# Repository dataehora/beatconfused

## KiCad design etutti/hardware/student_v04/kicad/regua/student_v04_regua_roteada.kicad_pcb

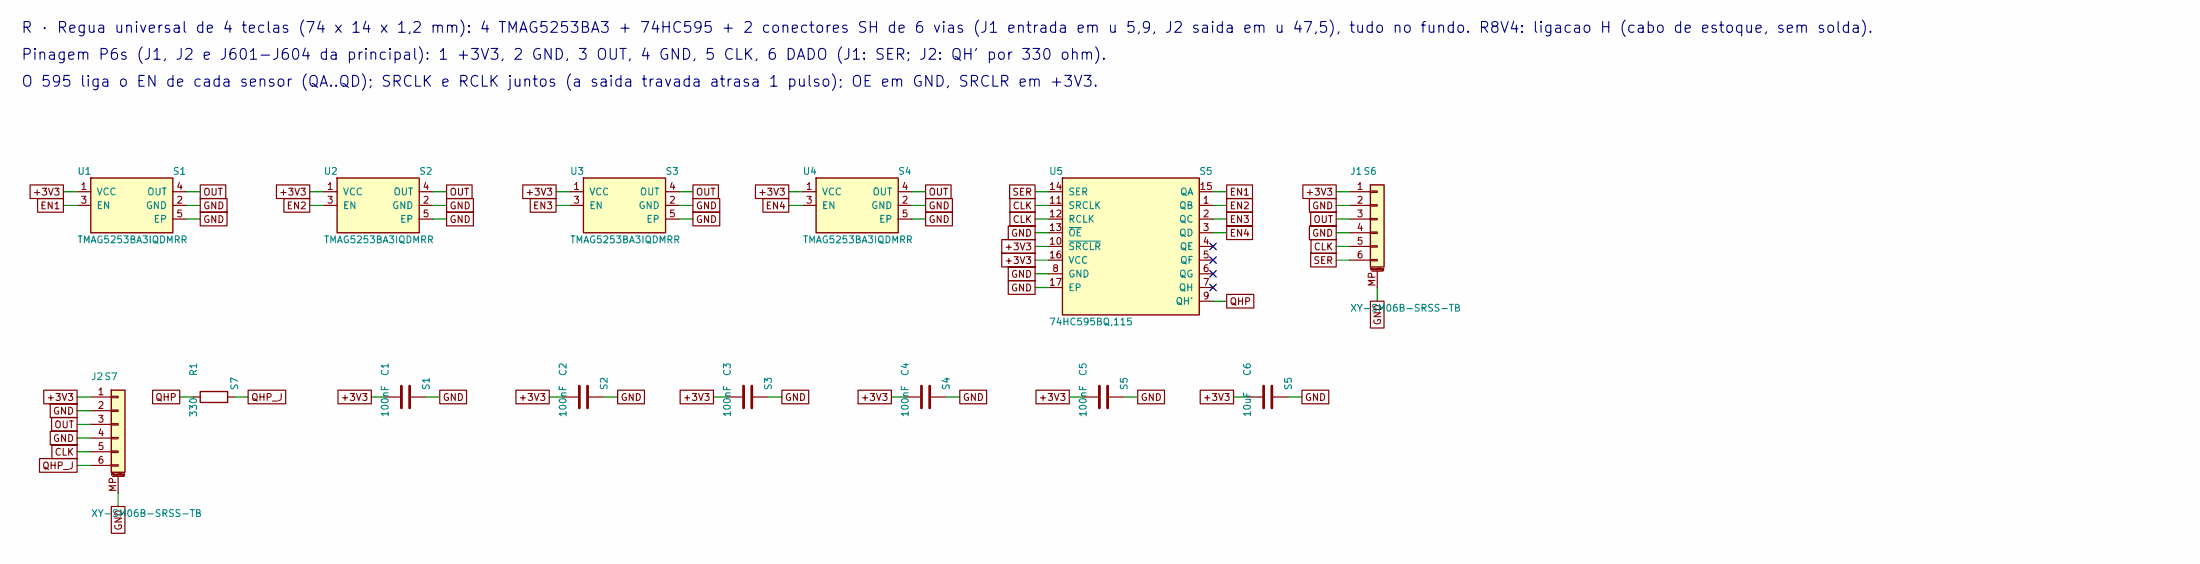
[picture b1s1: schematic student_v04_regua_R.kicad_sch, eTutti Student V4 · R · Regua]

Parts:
C1, C2, C3, C4, C5: 100nF; C_0402_1005Metric; LCSC C1525
C6: 10uF; C_0805_2012Metric; LCSC C15850
J1, J2: XY-SM06B-SRSS-TB; JST_SH_SM06B-SRSS-TB_1x06-1MP_P1.00mm_Horizontal; LCSC C56123098
R1: 330; R_0402_1005Metric; LCSC C25104
U1, U2, U3, U4: TMAG5253BA3IQDMRR; Texas_X2SON-4-1EP_1.1x1.4mm_P0.5mm_EP0.8x0.6mm; LCSC C22401868
U5: 74HC595BQ,115; DHVQFN-16-1EP_2.5x3.5mm_P0.5mm_EP1x2mm; LCSC C730243

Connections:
+3V3: C1.1, C2.1, C3.1, C4.1, C5.1, C6.1, J1.1, J2.1, U1.1 (VCC), U2.1 (VCC), U3.1 (VCC), U4.1 (VCC), U5.10 (~SRCLR), U5.16 (VCC)
CLK: J1.5, J2.5, U5.11 (SRCLK), U5.12 (RCLK)
EN1: U1.3 (EN), U5.15 (QA)
EN2: U2.3 (EN), U5.1 (QB)
EN3: U3.3 (EN), U5.2 (QC)
EN4: U4.3 (EN), U5.3 (QD)
GND: C1.2, C2.2, C3.2, C4.2, C5.2, C6.2, J1.2, J1.4, J1.MP (MountPin), J2.2, J2.4, J2.MP (MountPin), U1.2 (GND), U1.5 (EP), U2.2 (GND), U2.5 (EP), U3.2 (GND), U3.5 (EP), U4.2 (GND), U4.5 (EP), U5.8 (GND), U5.13 (~OE), U5.17 (EP)
OUT: J1.3, J2.3, U1.4 (OUT), U2.4 (OUT), U3.4 (OUT), U4.4 (OUT)
QHP: R1.1, U5.9 (QH')
QHP_J: J2.6, R1.2
SER: J1.6, U5.14 (SER)

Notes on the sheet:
R · Regua universal de 4 teclas (74 x 14 x 1,2 mm): 4 TMAG5253BA3 + 74HC595 + 2 conectores SH de 6 vias (J1 entrada em u 5,9, J2 saida em u 47,5), tudo no fundo. R8V4: ligacao H (cabo de estoque, sem solda).
Pinagem P6s (J1, J2 e J601-J604 da principal): 1 +3V3, 2 GND, 3 OUT, 4 GND, 5 CLK, 6 DADO (J1: SER; J2: QH' por 330 ohm).
O 595 liga o EN de cada sensor (QA..QD); SRCLK e RCLK juntos (a saida travada atrasa 1 pulso); OE em GND, SRCLR em +3V3.

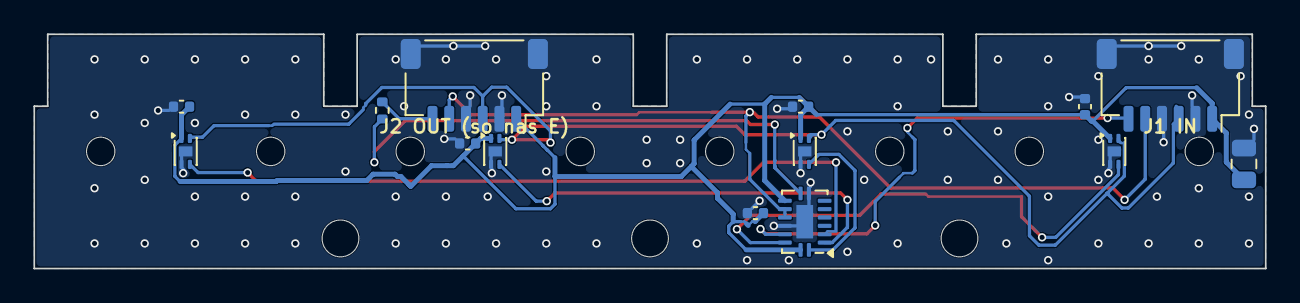
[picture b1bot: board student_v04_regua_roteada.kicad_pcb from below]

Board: 2 copper layers, 73.6 x 14.0 mm, 25 parts (14 on the bottom side), 11 nets.

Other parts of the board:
H1, H2, H3: MountingHole_2.2mm_M2
PEG1a, PEG1b, PEG2a, PEG2b, PEG3a, PEG3b, PEG4a, PEG4b: MountingHole_2.2mm_M2

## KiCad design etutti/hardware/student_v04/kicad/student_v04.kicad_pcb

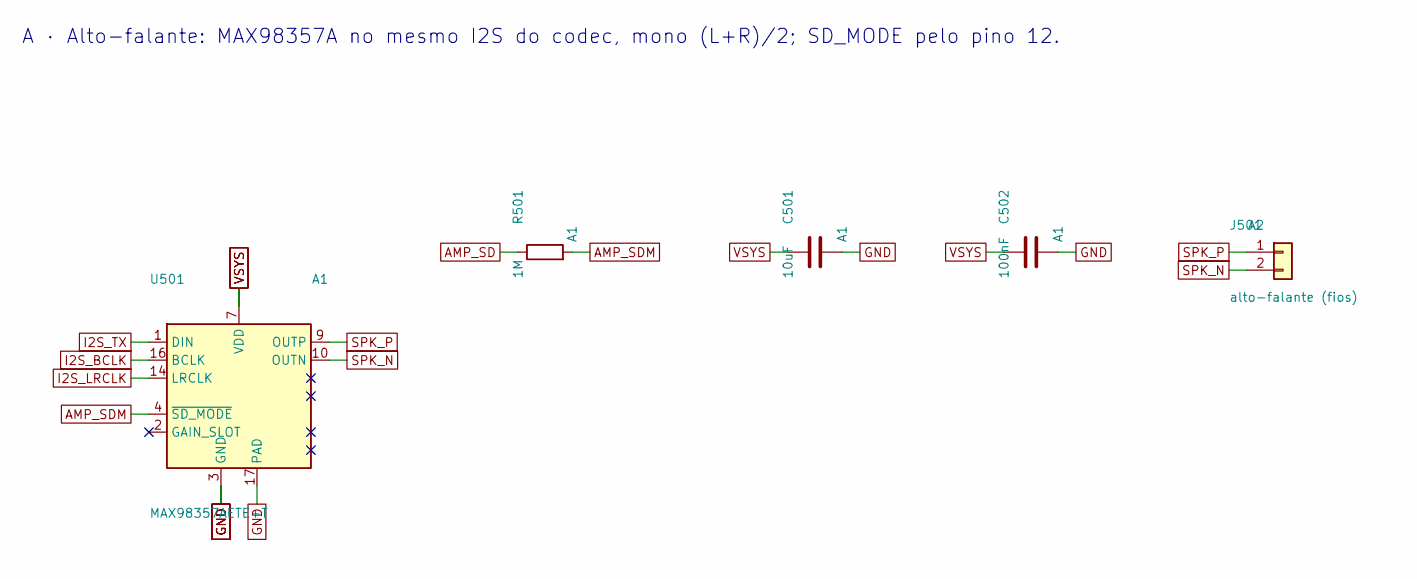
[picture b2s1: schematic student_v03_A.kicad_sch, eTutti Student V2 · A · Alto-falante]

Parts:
C501: 10uF; C_0805_2012Metric; LCSC C15850
C502: 100nF; C_0402_1005Metric; LCSC C1525
J501: alto-falante (fios); SolderWire-0.127sqmm_1x02_P3.7mm_D0.48mm_OD1mm
R501: 1M; R_0402_1005Metric; LCSC C26083
U501: MAX98357AETE+T; TQFN-16-1EP_3x3mm_P0.5mm_EP1.23x1.23mm; LCSC C910544

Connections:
AMP_SD: R501.1; also elsewhere on the board
AMP_SDM: R501.2, U501.4 (~SD_MODE)
GND: C501.2, C502.2, U501.3 (GND), U501.11 (GND), U501.15 (GND), U501.17 (PAD); also elsewhere on the board
I2S_BCLK: U501.16 (BCLK); also elsewhere on the board
I2S_LRCLK: U501.14 (LRCLK); also elsewhere on the board
I2S_TX: U501.1 (DIN); also elsewhere on the board
SPK_N: J501.2, U501.10 (OUTN)
SPK_P: J501.1, U501.9 (OUTP)
VSYS: C501.1, C502.1, U501.7 (VDD), U501.8 (VDD); also elsewhere on the board

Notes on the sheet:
A · Alto-falante: MAX98357A no mesmo I2S do codec, mono (L+R)/2; SD_MODE pelo pino 12.

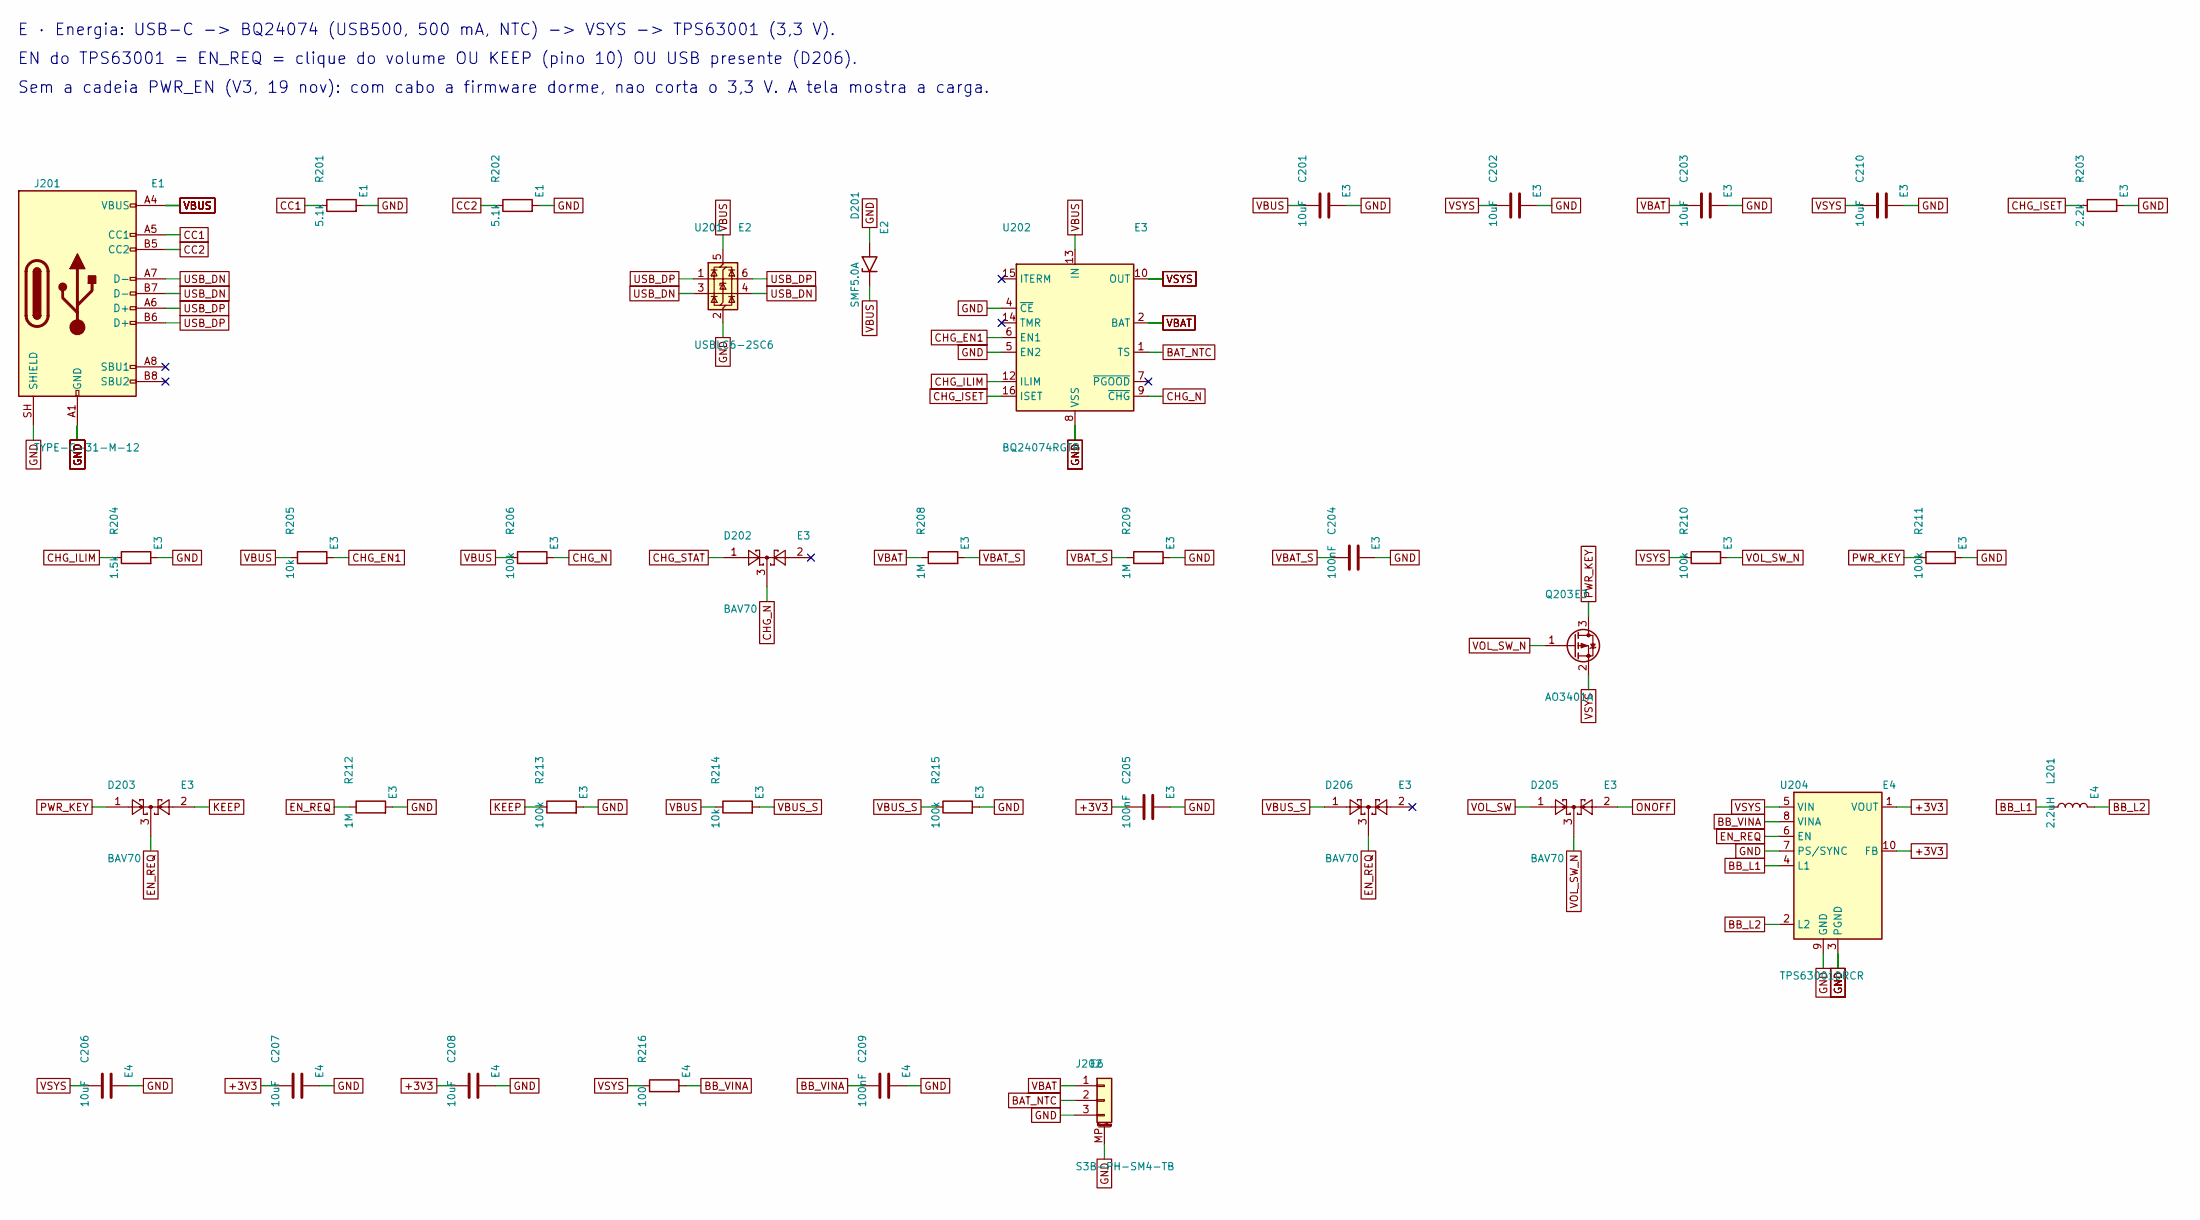
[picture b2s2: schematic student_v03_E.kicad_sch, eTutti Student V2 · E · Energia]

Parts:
C201, C202, C203, C206, C207, C208: 10uF; C_0805_2012Metric; LCSC C15850
C204, C205, C209: 100nF; C_0402_1005Metric; LCSC C1525
C210: 10uF; C_0603_1608Metric; LCSC C19702
D201: SMF5.0A; D_SOD-123F; LCSC C151296
D202, D203, D205, D206: BAV70; SOT-23; LCSC C68978
J201: TYPE-C-31-M-12; USB_C_Receptacle_HRO_TYPE-C-31-M-12; LCSC C165948
J202: S3B-PH-SM4-TB; JST_PH_S3B-PH-SM4-TB_1x03-1MP_P2.00mm_Horizontal; LCSC C265101
L201: 2.2uH; L_Changjiang_FNR4020S; LCSC C167825
Q203: AO3401A; SOT-23; LCSC C15127
R201, R202: 5.1k; R_0402_1005Metric; LCSC C25905
R203: 2.2k; R_0402_1005Metric; LCSC C25879
R204: 1.5k; R_0402_1005Metric; LCSC C25867
R205, R214: 10k; R_0402_1005Metric; LCSC C25744
R206, R210, R211, R213, R215: 100k; R_0402_1005Metric; LCSC C25741
R208, R209, R212: 1M; R_0402_1005Metric; LCSC C26083
R216: 100; R_0402_1005Metric; LCSC C25076
U201: USBLC6-2SC6; SOT-23-6; LCSC C7519
U202: BQ24074RGTR; VQFN-16-1EP_3x3mm_P0.5mm_EP1.6x1.6mm; LCSC C54313
U204: TPS63001DRCR; Texas_DRC0010J; LCSC C28060

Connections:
+3V3: C205.1, C207.1, C208.1, U204.1 (VOUT), U204.10 (FB); also elsewhere on the board
BAT_NTC: J202.2, U202.1 (TS)
BB_L1: L201.1, U204.4 (L1)
BB_L2: L201.2, U204.2 (L2)
BB_VINA: C209.1, R216.2, U204.8 (VINA)
CC1: J201.A5 (CC1), R201.1
CC2: J201.B5 (CC2), R202.1
CHG_EN1: R205.2, U202.6 (EN1)
CHG_ILIM: R204.1, U202.12 (ILIM)
CHG_ISET: R203.1, U202.16 (ISET)
CHG_N: D202.3, R206.2, U202.9 (~CHG)
CHG_STAT: D202.1; also elsewhere on the board
EN_REQ: D203.3, D206.3, R212.1, U204.6 (EN)
GND: C201.2, C202.2, C203.2, C204.2, C205.2, C206.2, C207.2, C208.2, C209.2, C210.2, D201.2 (A2), J201.A1 (GND), J201.A12 (GND), J201.B1 (GND), J201.B12 (GND), J201.SH (SHIELD), J202.3, J202.MP (MountPin), R201.2, R202.2, R203.2, R204.2, R209.2, R211.2, R212.2, R213.2, R215.2, U201.2 (GND), U202.4 (~CE), U202.5 (EN2), U202.8 (VSS), U202.17 (VSS), U204.3 (PGND), U204.7 (PS/SYNC), U204.9 (GND), U204.11 (PGND); also elsewhere on the board
KEEP: D203.2, R213.1; also elsewhere on the board
ONOFF: D205.2; also elsewhere on the board
PWR_KEY: D203.1, Q203.3 (D), R211.1
USB_DN: J201.A7 (D-), J201.B7 (D-), U201.3 (I/O2), U201.4 (I/O2); also elsewhere on the board
USB_DP: J201.A6 (D+), J201.B6 (D+), U201.1 (I/O1), U201.6 (I/O1); also elsewhere on the board
VBAT: C203.1, J202.1, R208.1, U202.2 (BAT), U202.3 (BAT)
VBAT_S: C204.1, R208.2, R209.1; also elsewhere on the board
VBUS: C201.1, D201.1 (A1), J201.A4 (VBUS), J201.A9 (VBUS), J201.B4 (VBUS), J201.B9 (VBUS), R205.1, R206.1, R214.1, U201.5 (VBUS), U202.13 (IN); also elsewhere on the board
VBUS_S: D206.1, R214.2, R215.1
VOL_SW: D205.1; also elsewhere on the board
VOL_SW_N: D205.3, Q203.1 (G), R210.2; also elsewhere on the board
VSYS: C202.1, C206.1, C210.1, Q203.2 (S), R210.1, R216.1, U202.10 (OUT), U202.11 (OUT), U204.5 (VIN); also elsewhere on the board

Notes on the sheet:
E · Energia: USB-C -> BQ24074 (USB500, 500 mA, NTC) -> VSYS -> TPS63001 (3,3 V).
EN do TPS63001 = EN_REQ = clique do volume OU KEEP (pino 10) OU USB presente (D206).
Sem a cadeia PWR_EN (V3, 19 nov): com cabo a firmware dorme, nao corta o 3,3 V. A tela mostra a carga.

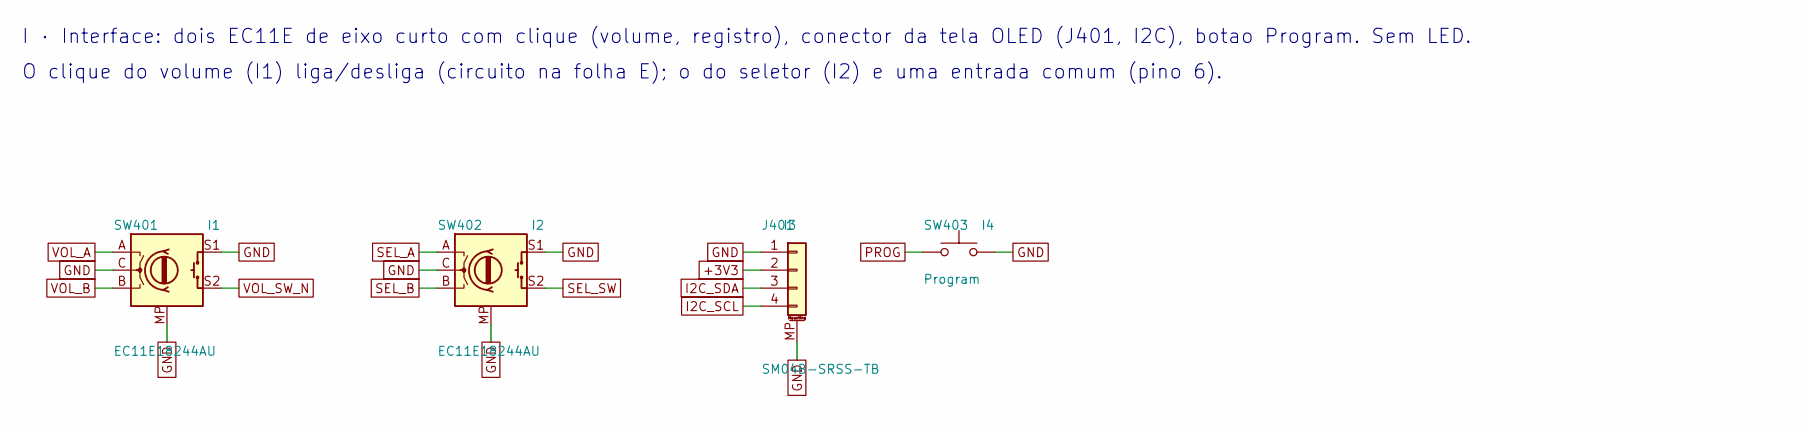
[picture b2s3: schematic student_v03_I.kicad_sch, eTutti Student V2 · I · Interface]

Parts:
J401: SM04B-SRSS-TB; JST_SH_SM04B-SRSS-TB_1x04-1MP_P1.00mm_Horizontal; LCSC C160404
SW401, SW402: EC11E18244AU; RotaryEncoder_Alps_EC11E-Switch_Vertical_H20mm; LCSC C202365
SW403: Program; SW_Push_1P1T_XKB_TS-1187A; LCSC C318884

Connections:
+3V3: J401.2; also elsewhere on the board
GND: J401.1, J401.MP (MountPin), SW401.C, SW401.MP, SW401.S1, SW402.C, SW402.MP, SW402.S1, SW403.2; also elsewhere on the board
I2C_SCL: J401.4; also elsewhere on the board
I2C_SDA: J401.3; also elsewhere on the board
PROG: SW403.1; also elsewhere on the board
SEL_A: SW402.A; also elsewhere on the board
SEL_B: SW402.B; also elsewhere on the board
SEL_SW: SW402.S2; also elsewhere on the board
VOL_A: SW401.A; also elsewhere on the board
VOL_B: SW401.B; also elsewhere on the board
VOL_SW_N: SW401.S2; also elsewhere on the board

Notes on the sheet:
I · Interface: dois EC11E de eixo curto com clique (volume, registro), conector da tela OLED (J401, I2C), botao Program. Sem LED.
O clique do volume (I1) liga/desliga (circuito na folha E); o do seletor (I2) e uma entrada comum (pino 6).

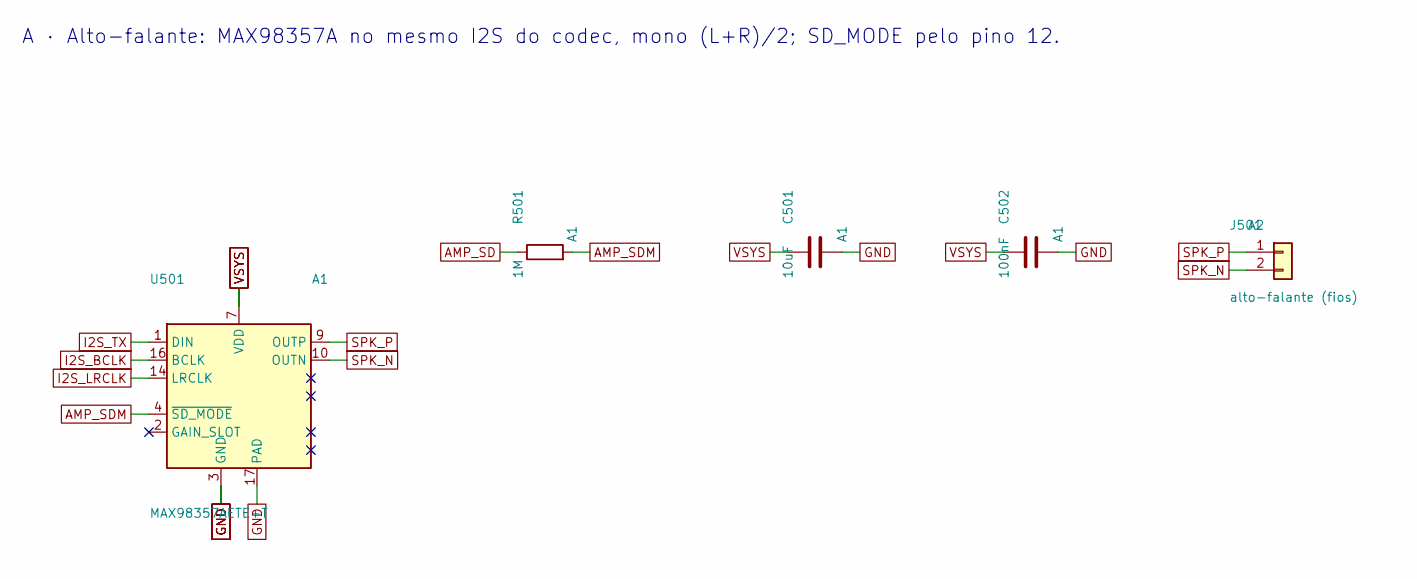
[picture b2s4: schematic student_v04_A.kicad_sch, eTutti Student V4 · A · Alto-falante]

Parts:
C501: 10uF; C_0805_2012Metric; LCSC C15850
C502: 100nF; C_0402_1005Metric; LCSC C1525
J501: alto-falante (fios); SolderWire-0.127sqmm_1x02_P3.7mm_D0.48mm_OD1mm
R501: 1M; R_0402_1005Metric; LCSC C26083
U501: MAX98357AETE+T; TQFN-16-1EP_3x3mm_P0.5mm_EP1.23x1.23mm; LCSC C910544

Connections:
AMP_SD: R501.1; also elsewhere on the board
AMP_SDM: R501.2, U501.4 (~SD_MODE)
GND: C501.2, C502.2, U501.3 (GND), U501.11 (GND), U501.15 (GND), U501.17 (PAD); also elsewhere on the board
I2S_BCLK: U501.16 (BCLK); also elsewhere on the board
I2S_LRCLK: U501.14 (LRCLK); also elsewhere on the board
I2S_TX: U501.1 (DIN); also elsewhere on the board
SPK_N: J501.2, U501.10 (OUTN)
SPK_P: J501.1, U501.9 (OUTP)
VSYS: C501.1, C502.1, U501.7 (VDD), U501.8 (VDD); also elsewhere on the board

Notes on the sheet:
A · Alto-falante: MAX98357A no mesmo I2S do codec, mono (L+R)/2; SD_MODE pelo pino 12.

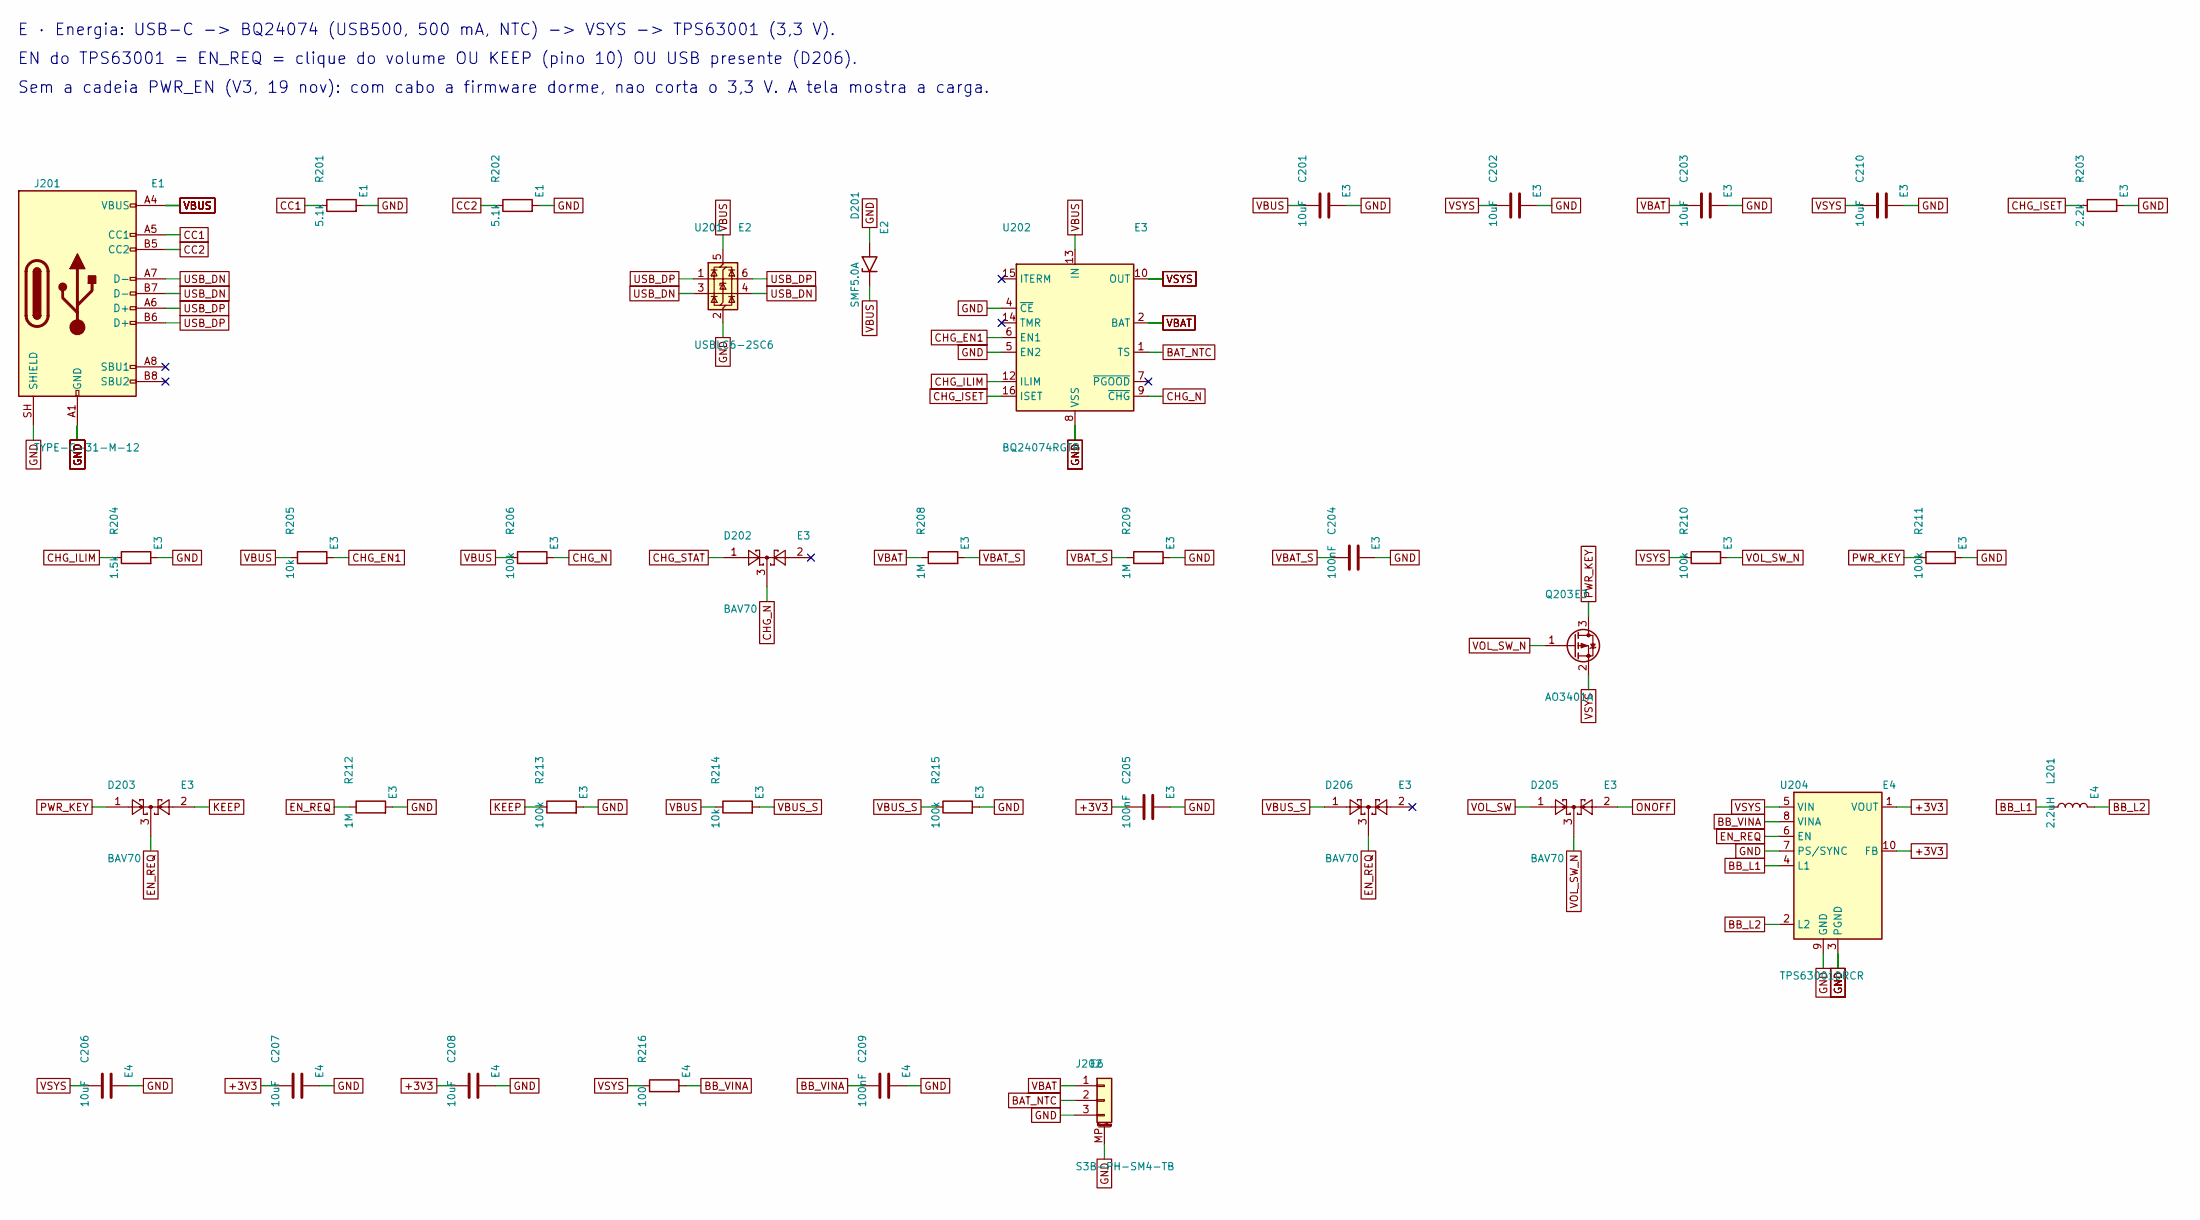
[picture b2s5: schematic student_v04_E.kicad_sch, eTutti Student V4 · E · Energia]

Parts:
C201, C202, C203, C206, C207, C208: 10uF; C_0805_2012Metric; LCSC C15850
C204, C205, C209: 100nF; C_0402_1005Metric; LCSC C1525
C210: 10uF; C_0603_1608Metric; LCSC C19702
D201: SMF5.0A; D_SOD-123F; LCSC C151296
D202, D203, D205, D206: BAV70; SOT-23; LCSC C68978
J201: TYPE-C-31-M-12; USB_C_Receptacle_HRO_TYPE-C-31-M-12; LCSC C165948
J202: S3B-PH-SM4-TB; JST_PH_S3B-PH-SM4-TB_1x03-1MP_P2.00mm_Horizontal; LCSC C265101
L201: 2.2uH; L_Changjiang_FNR4020S; LCSC C167825
Q203: AO3401A; SOT-23; LCSC C15127
R201, R202: 5.1k; R_0402_1005Metric; LCSC C25905
R203: 2.2k; R_0402_1005Metric; LCSC C25879
R204: 1.5k; R_0402_1005Metric; LCSC C25867
R205, R214: 10k; R_0402_1005Metric; LCSC C25744
R206, R210, R211, R213, R215: 100k; R_0402_1005Metric; LCSC C25741
R208, R209, R212: 1M; R_0402_1005Metric; LCSC C26083
R216: 100; R_0402_1005Metric; LCSC C25076
U201: USBLC6-2SC6; SOT-23-6; LCSC C7519
U202: BQ24074RGTR; VQFN-16-1EP_3x3mm_P0.5mm_EP1.6x1.6mm; LCSC C54313
U204: TPS63001DRCR; Texas_DRC0010J; LCSC C28060

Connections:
+3V3: C205.1, C207.1, C208.1, U204.1 (VOUT), U204.10 (FB); also elsewhere on the board
BAT_NTC: J202.2, U202.1 (TS)
BB_L1: L201.1, U204.4 (L1)
BB_L2: L201.2, U204.2 (L2)
BB_VINA: C209.1, R216.2, U204.8 (VINA)
CC1: J201.A5 (CC1), R201.1
CC2: J201.B5 (CC2), R202.1
CHG_EN1: R205.2, U202.6 (EN1)
CHG_ILIM: R204.1, U202.12 (ILIM)
CHG_ISET: R203.1, U202.16 (ISET)
CHG_N: D202.3, R206.2, U202.9 (~CHG)
CHG_STAT: D202.1; also elsewhere on the board
EN_REQ: D203.3, D206.3, R212.1, U204.6 (EN)
GND: C201.2, C202.2, C203.2, C204.2, C205.2, C206.2, C207.2, C208.2, C209.2, C210.2, D201.2 (A2), J201.A1 (GND), J201.A12 (GND), J201.B1 (GND), J201.B12 (GND), J201.SH (SHIELD), J202.3, J202.MP (MountPin), R201.2, R202.2, R203.2, R204.2, R209.2, R211.2, R212.2, R213.2, R215.2, U201.2 (GND), U202.4 (~CE), U202.5 (EN2), U202.8 (VSS), U202.17 (VSS), U204.3 (PGND), U204.7 (PS/SYNC), U204.9 (GND), U204.11 (PGND); also elsewhere on the board
KEEP: D203.2, R213.1; also elsewhere on the board
ONOFF: D205.2; also elsewhere on the board
PWR_KEY: D203.1, Q203.3 (D), R211.1
USB_DN: J201.A7 (D-), J201.B7 (D-), U201.3 (I/O2), U201.4 (I/O2); also elsewhere on the board
USB_DP: J201.A6 (D+), J201.B6 (D+), U201.1 (I/O1), U201.6 (I/O1); also elsewhere on the board
VBAT: C203.1, J202.1, R208.1, U202.2 (BAT), U202.3 (BAT)
VBAT_S: C204.1, R208.2, R209.1; also elsewhere on the board
VBUS: C201.1, D201.1 (A1), J201.A4 (VBUS), J201.A9 (VBUS), J201.B4 (VBUS), J201.B9 (VBUS), R205.1, R206.1, R214.1, U201.5 (VBUS), U202.13 (IN); also elsewhere on the board
VBUS_S: D206.1, R214.2, R215.1
VOL_SW: D205.1; also elsewhere on the board
VOL_SW_N: D205.3, Q203.1 (G), R210.2; also elsewhere on the board
VSYS: C202.1, C206.1, C210.1, Q203.2 (S), R210.1, R216.1, U202.10 (OUT), U202.11 (OUT), U204.5 (VIN); also elsewhere on the board

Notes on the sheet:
E · Energia: USB-C -> BQ24074 (USB500, 500 mA, NTC) -> VSYS -> TPS63001 (3,3 V).
EN do TPS63001 = EN_REQ = clique do volume OU KEEP (pino 10) OU USB presente (D206).
Sem a cadeia PWR_EN (V3, 19 nov): com cabo a firmware dorme, nao corta o 3,3 V. A tela mostra a carga.

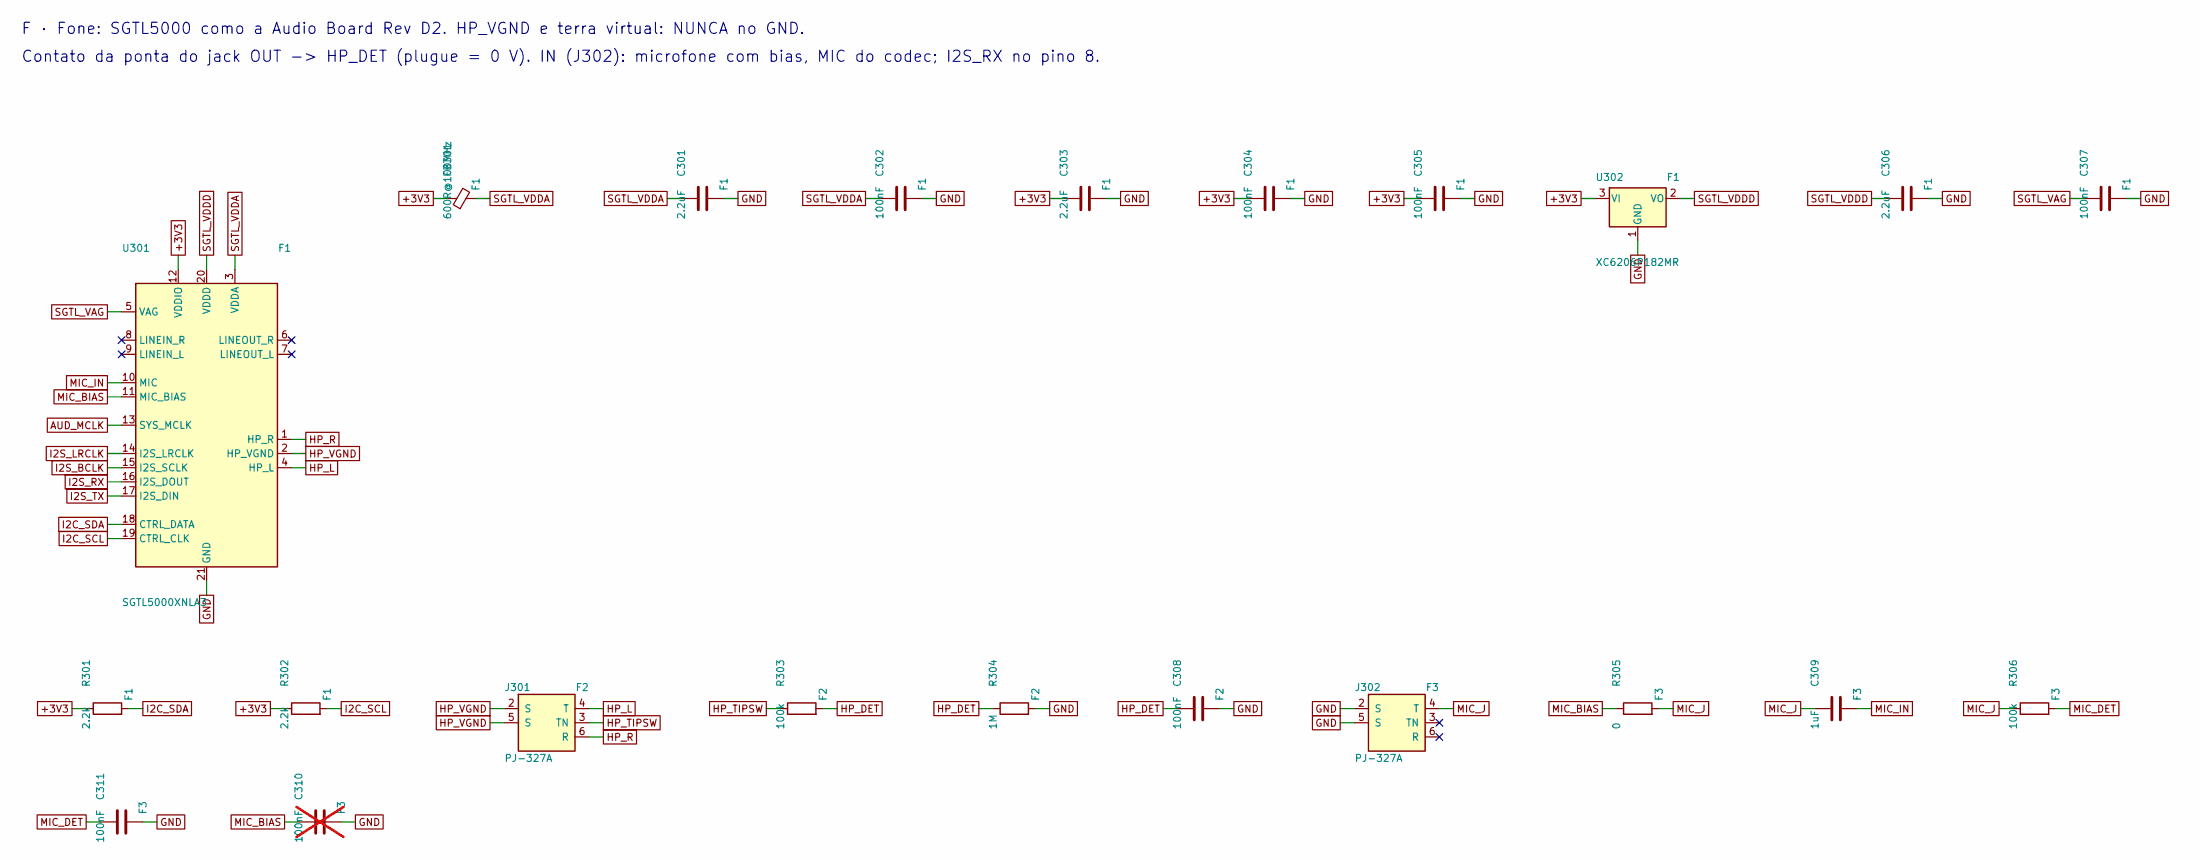
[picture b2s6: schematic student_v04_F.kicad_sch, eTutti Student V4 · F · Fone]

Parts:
C301, C303, C306: 2.2uF; C_0402_1005Metric; LCSC C12530
C302, C304, C305, C307, C308, C311: 100nF; C_0402_1005Metric; LCSC C1525
C309: 1uF; C_0402_1005Metric; LCSC C52923
C310: 100nF; C_0402_1005Metric; LCSC C1525; not fitted
FB301: 600R@100MHz; L_0603_1608Metric; LCSC C1002
J301, J302: PJ-327A; Jack_3.5mm_PJ-327A_SMD; LCSC C49284723
R301, R302: 2.2k; R_0402_1005Metric; LCSC C25879
R303, R306: 100k; R_0402_1005Metric; LCSC C25741
R304: 1M; R_0402_1005Metric; LCSC C26083
R305: 0; R_0402_1005Metric; LCSC C17168
U301: SGTL5000XNLA3; QFN-20-1EP_3x3mm_P0.4mm_EP1.65x1.65mm; LCSC C2651833
U302: XC6206P182MR; SOT-23-3; LCSC C347373

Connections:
+3V3: C303.1, C304.1, C305.1, FB301.1, R301.1, R302.1, U301.12 (VDDIO), U302.3 (VI); also elsewhere on the board
AUD_MCLK: U301.13 (SYS_MCLK); also elsewhere on the board
GND: C301.2, C302.2, C303.2, C304.2, C305.2, C306.2, C307.2, C308.2, C310.2, C311.2, J302.2 (S), J302.5 (S), R304.2, U301.21 (GND), U302.1 (GND); also elsewhere on the board
HP_DET: C308.1, R303.2, R304.1; also elsewhere on the board
HP_L: J301.4 (T), U301.4 (HP_L)
HP_R: J301.6 (R), U301.1 (HP_R)
HP_TIPSW: J301.3 (TN), R303.1
HP_VGND: J301.2 (S), J301.5 (S), U301.2 (HP_VGND)
I2C_SCL: R302.2, U301.19 (CTRL_CLK); also elsewhere on the board
I2C_SDA: R301.2, U301.18 (CTRL_DATA); also elsewhere on the board
I2S_BCLK: U301.15 (I2S_SCLK); also elsewhere on the board
I2S_LRCLK: U301.14 (I2S_LRCLK); also elsewhere on the board
I2S_RX: U301.16 (I2S_DOUT); also elsewhere on the board
I2S_TX: U301.17 (I2S_DIN); also elsewhere on the board
MIC_BIAS: C310.1, R305.1, U301.11 (MIC_BIAS)
MIC_DET: C311.1, R306.2; also elsewhere on the board
MIC_IN: C309.2, U301.10 (MIC)
MIC_J: C309.1, J302.4 (T), R305.2, R306.1
SGTL_VAG: C307.1, U301.5 (VAG)
SGTL_VDDA: C301.1, C302.1, FB301.2, U301.3 (VDDA)
SGTL_VDDD: C306.1, U301.20 (VDDD), U302.2 (VO)

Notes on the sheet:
F · Fone: SGTL5000 como a Audio Board Rev D2. HP_VGND e terra virtual: NUNCA no GND.
Contato da ponta do jack OUT -> HP_DET (plugue = 0 V). IN (J302): microfone com bias, MIC do codec; I2S_RX no pino 8.

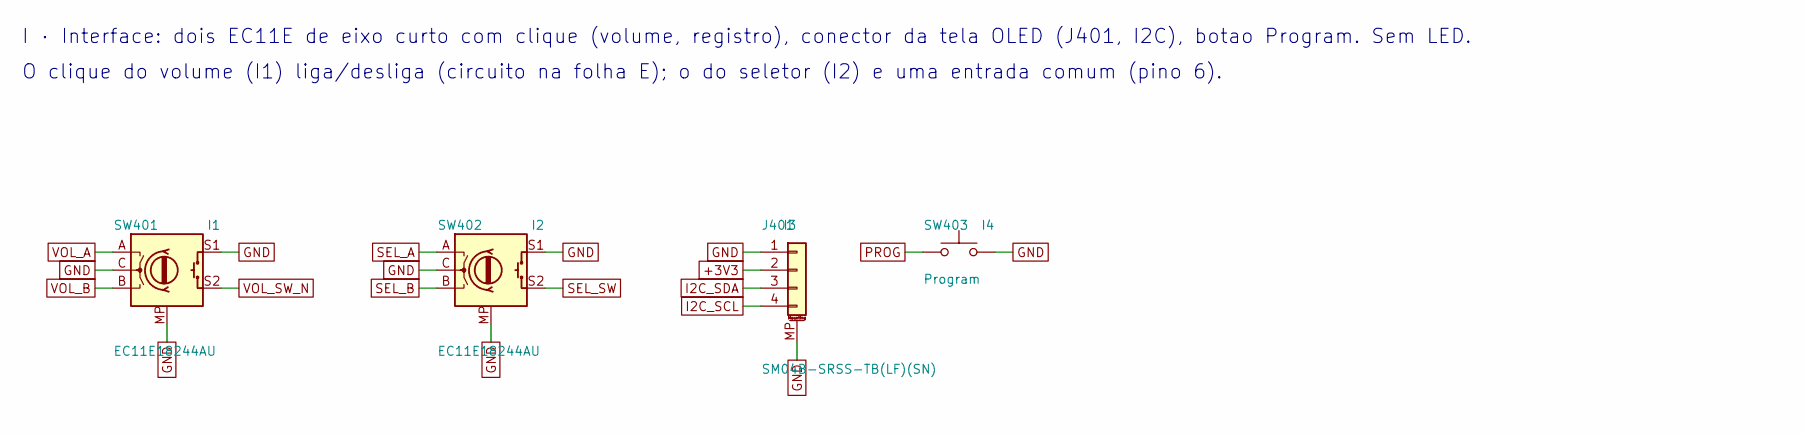
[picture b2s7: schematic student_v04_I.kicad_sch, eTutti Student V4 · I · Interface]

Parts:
J401: SM04B-SRSS-TB(LF)(SN); JST_SH_SM04B-SRSS-TB_1x04-1MP_P1.00mm_Horizontal; LCSC C160404
SW401, SW402: EC11E18244AU; RotaryEncoder_Alps_EC11E-Switch_Vertical_H20mm; LCSC C202365
SW403: Program; SW_Push_1P1T_XKB_TS-1187A; LCSC C318884

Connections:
+3V3: J401.2; also elsewhere on the board
GND: J401.1, J401.MP (MountPin), SW401.C, SW401.MP, SW401.S1, SW402.C, SW402.MP, SW402.S1, SW403.2; also elsewhere on the board
I2C_SCL: J401.4; also elsewhere on the board
I2C_SDA: J401.3; also elsewhere on the board
PROG: SW403.1; also elsewhere on the board
SEL_A: SW402.A; also elsewhere on the board
SEL_B: SW402.B; also elsewhere on the board
SEL_SW: SW402.S2; also elsewhere on the board
VOL_A: SW401.A; also elsewhere on the board
VOL_B: SW401.B; also elsewhere on the board
VOL_SW_N: SW401.S2; also elsewhere on the board

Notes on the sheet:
I · Interface: dois EC11E de eixo curto com clique (volume, registro), conector da tela OLED (J401, I2C), botao Program. Sem LED.
O clique do volume (I1) liga/desliga (circuito na folha E); o do seletor (I2) e uma entrada comum (pino 6).
